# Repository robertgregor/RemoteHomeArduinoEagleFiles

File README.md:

RemoteHomeArduinoEagleFiles
===========================

Remote Home Eagle files for the boards

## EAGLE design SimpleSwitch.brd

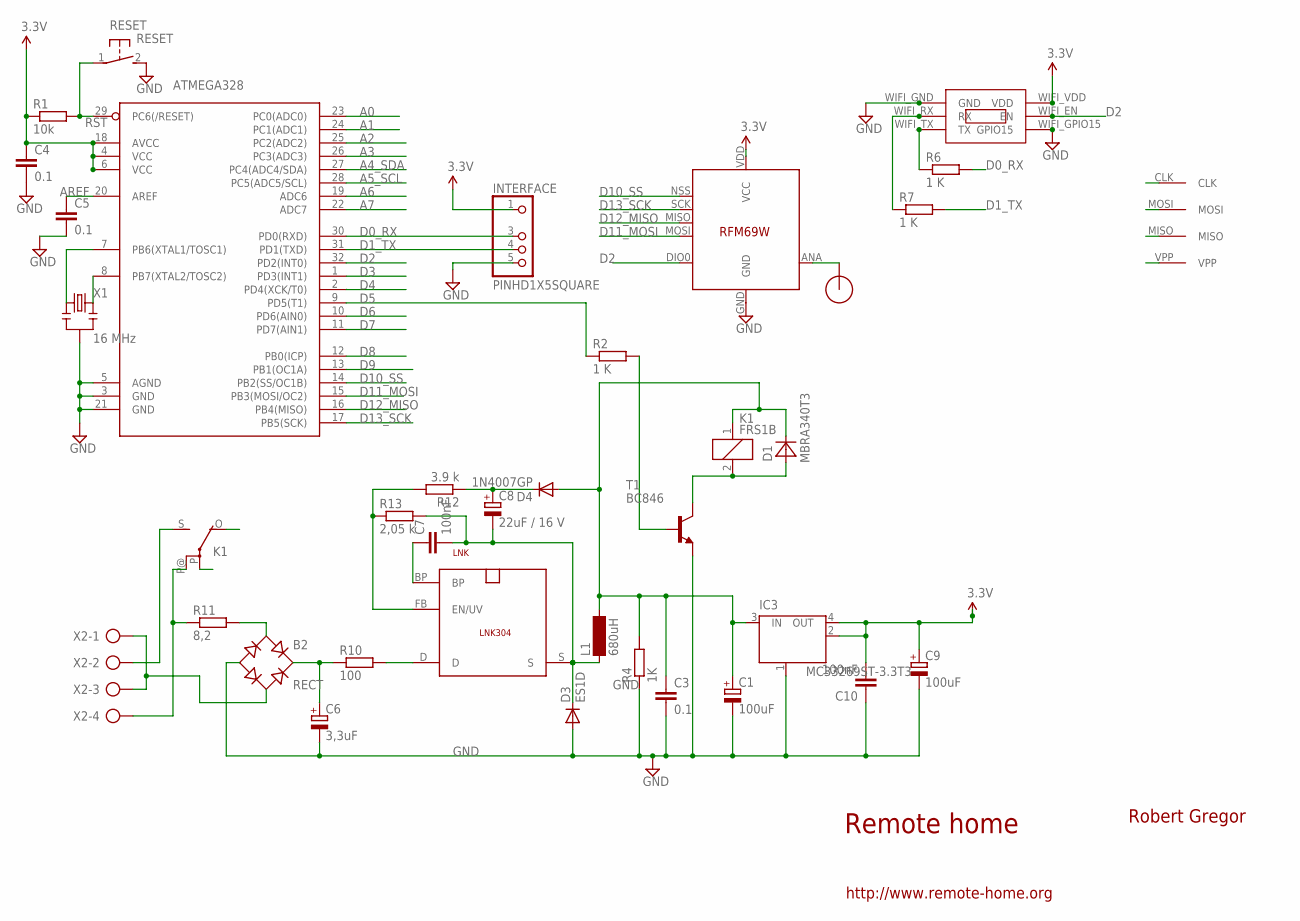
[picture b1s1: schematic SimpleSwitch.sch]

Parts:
ATMEGA328: ATMega-328; TQFP32-08
B2: RECT; TO-269AA
C1, C9: 100uF; SMC_B
C3, C4, C5: 0.1; C2012
C6: 3,3uF; E5-10,5
C7, C10: 100nF; C2012
C8: 22uF / 16 V; SMC_C
D1: MBRA340T3; SMA
D3: ES1D; DO214AC
D4: 1N4007GP; DO214AA
IC3: MC33269ST-3.3T3; SOT223
INTERFACE: PINHD1X5SQUARE; PINHD1X05-SQUARE
K1: FRS1B
L1: 680uH; BS11
LNK: LNK304; SO-8C
R1: 10k; R2012
R2, R6, R7: 1 K; M2012
R4: 1K; M2012
R10: 100; R2512W
R11: 8,2; 0411/12
R12: 3.9 k; M2012
R13: 2,05 k; M2012
RESET: RESET; DTSM-3
RFM69: RFM69W
T1: BC846; SOT23
U$1: RFM12B_ANTENNA; RFM12B-ANTENNA
U$2: AVRHEADERDIP; AVRHEADER
U$5: ESP03
X1: 16 MHz; RESONATOR-SMD
X2: AK500/4

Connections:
5V: C1.+, C3.1, D1.C, D4.A, IC3.3 (IN), K1.1, L1.2, R4.2
A0: ATMEGA328.23 (PC0(ADC0))
A1: ATMEGA328.24 (PC1(ADC1))
A2: ATMEGA328.25 (PC2(ADC2))
A3: ATMEGA328.26 (PC3(ADC3))
A4_SDA: ATMEGA328.27 (PC4(ADC4/SDA))
A5_SCL: ATMEGA328.28 (PC5(ADC5/SCL))
A6: ATMEGA328.19 (ADC6)
A7: ATMEGA328.22 (ADC7)
AREF: ATMEGA328.20 (AREF), C5.1
D0_RX: ATMEGA328.30 (PD0(RXD)), INTERFACE.3, R6.2
D1_TX: ATMEGA328.31 (PD1(TXD)), INTERFACE.4, R7.2
D2: ATMEGA328.32 (PD2(INT0)), RFM69.DIO0, U$5.WIFI_EN (EN)
D3: ATMEGA328.1 (PD3(INT1))
D4: ATMEGA328.2 (PD4(XCK/T0))
D5: ATMEGA328.9 (PD5(T1)), R2.1
D6: ATMEGA328.10 (PD6(AIN0))
D7: ATMEGA328.11 (PD7(AIN1))
D8: ATMEGA328.12 (PB0(ICP))
D9: ATMEGA328.13 (PB1(OC1A))
D10_SS: ATMEGA328.14 (PB2(SS/OC1B)), RFM69.NSS (SEL)
D11_MOSI: ATMEGA328.15 (PB3(MOSI/OC2)), RFM69.MOSI, U$2.MOSI
D12_MISO: ATMEGA328.16 (PB4(MISO)), RFM69.MISO, U$2.MISO
D13_SCK: ATMEGA328.17 (PB5(SCK)), RFM69.SCK, U$2.CLK
FB: LNK.FB (EN/UV), R12.2, R13.1
GND: ATMEGA328.3 (GND), ATMEGA328.5 (AGND), ATMEGA328.21 (GND), B2.-, C1.-, C3.2, C4.2, C5.2, C6.-, C9.-, C10.1, D3.A, IC3.1 (GND/ADJ), INTERFACE.5, R4.1, RESET.2, RFM69.GND, T1.2 (E), U$5.WIFI_GND (GND), U$5.WIFI_GPIO15 (GPIO15), X1.2
unnamed: ATMEGA328.7 (PB6(XTAL1/TOSC1)), X1.1
unnamed: R2.2, T1.1 (B)
unnamed: RFM69.ANA (ANT), U$1.P$1
unnamed: D1.A, K1.2, T1.3 (C)
unnamed: K1.S, X2.2
unnamed: K1.P@, R11.1, X2.4
unnamed: B2.AC2, X2.1, X2.3
unnamed: R6.1, U$5.WIFI_TX (TX)
unnamed: R7.1, U$5.WIFI_RX (RX)
unnamed: LNK.D, R10.2
unnamed: B2.+, C6.+, R10.1
unnamed: B2.AC1, R11.2
unnamed: C7.1, LNK.BP
unnamed: C8.+, D4.C, R12.1
unnamed: ATMEGA328.8 (PB7(XTAL2/TOSC2)), X1.3
RST: ATMEGA328.29 (PC6(/RESET)), R1.2, RESET.1, U$2.VPP
S: C7.2, C8.-, D3.C, L1.1, LNK.S, R13.2
VCC: ATMEGA328.4 (VCC), ATMEGA328.6 (VCC), ATMEGA328.18 (AVCC), C4.1, C9.+, C10.2, IC3.2 (OUT), IC3.4 (OUT), INTERFACE.1, R1.1, RFM69.VDD (VCC), U$5.WIFI_VDD (VDD)

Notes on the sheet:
Remote home
Robert Gregor
http://www.remote-home.org

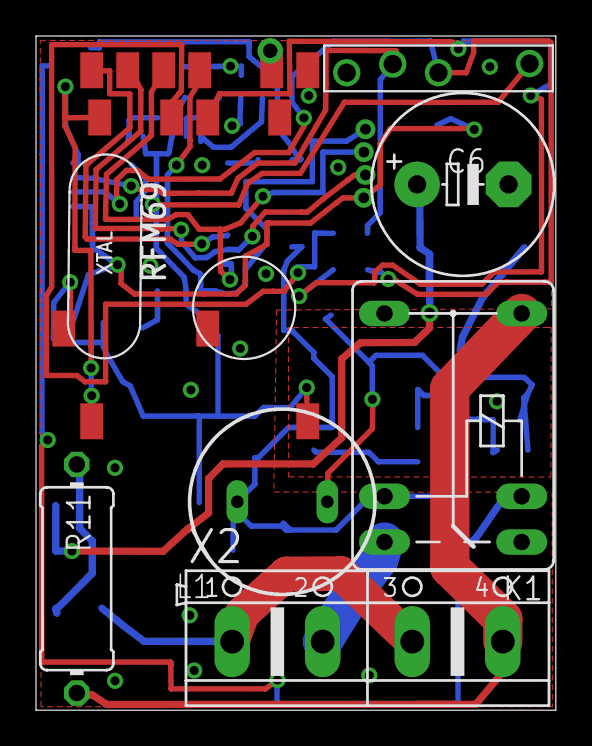
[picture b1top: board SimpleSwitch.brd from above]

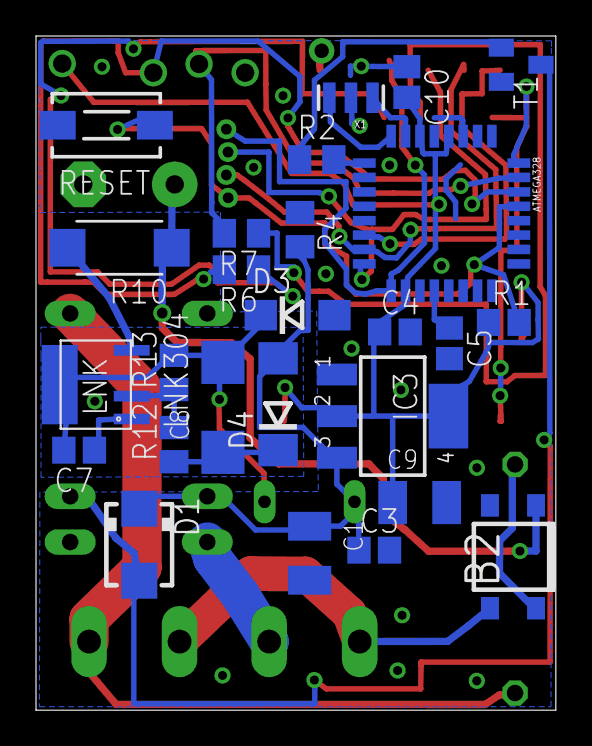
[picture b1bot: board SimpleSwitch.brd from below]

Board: 2 copper layers, 28.9 x 37.5 mm, 36 parts (26 on the bottom side), 30 nets.

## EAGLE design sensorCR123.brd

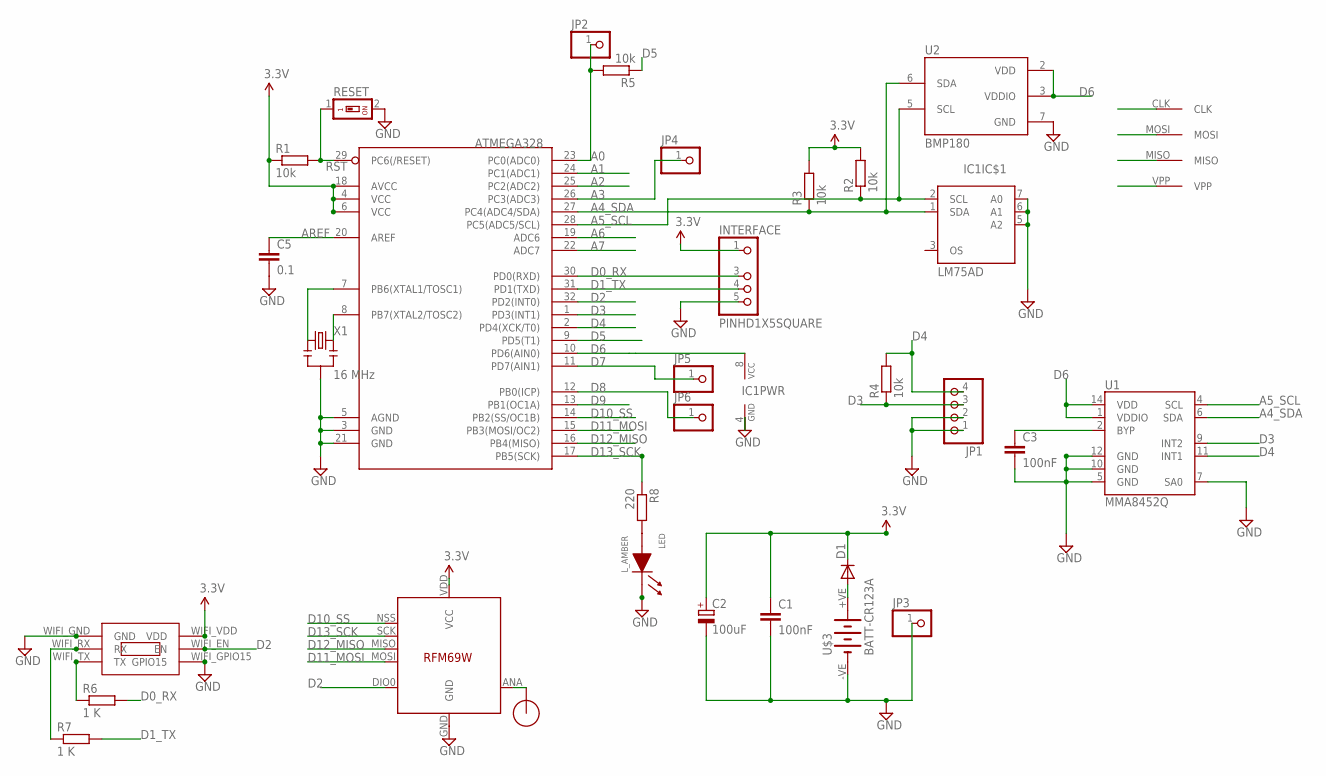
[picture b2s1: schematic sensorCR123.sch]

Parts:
ATMEGA328: ATMega-328; TQFP32-08
C1, C3: 100nF; C2012
C2: 100uF; SMC_B
C5: 0.1; C2012
D1: DIODE-DO214BA; DO214BA
IC1: LM75AD; SO08
INTERFACE: PINHD1X5SQUARE; PINHD1X05-SQUARE
JP1: PINHD-1X04_2.54-S; 1X04-S
JP2, JP3, JP4, JP5, JP6: PINHD-1X01_2.54; 1X01
LED: L_AMBER; LED0805
R1, R2, R3, R4, R5: 10k; R2012
R6, R7: 1 K; M2012
R8: 220; M2012
RESET: SWS001; SMS-001
U1: MMA8452Q; QFN-16_0.5MM
U2: BMP180
U$1: RFM12B_ANTENNA; RFM12B-ANTENNA
U$2: AVRHEADERDIP; AVRHEADER
U$3: BATT-CR123A; KEYSTONE-2/3A
U$4: RFM69W
U$5: ESP03
X1: 16 MHz; RESONATOR-SMD

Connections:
A0: ATMEGA328.23 (PC0(ADC0)), JP2.1, R5.2
A1: ATMEGA328.24 (PC1(ADC1))
A2: ATMEGA328.25 (PC2(ADC2))
A3: ATMEGA328.26 (PC3(ADC3)), JP4.1
A4_SDA: ATMEGA328.27 (PC4(ADC4/SDA)), IC1.1 (SDA), R3.1, U1.6 (SDA), U2.6 (SDA)
A5_SCL: ATMEGA328.28 (PC5(ADC5/SCL)), IC1.2 (SCL), R2.1, U1.4 (SCL), U2.5 (SCL)
A6: ATMEGA328.19 (ADC6)
A7: ATMEGA328.22 (ADC7)
AREF: ATMEGA328.20 (AREF), C5.1
D0_RX: ATMEGA328.30 (PD0(RXD)), INTERFACE.3, R6.2
D1_TX: ATMEGA328.31 (PD1(TXD)), INTERFACE.4, R7.2
D2: ATMEGA328.32 (PD2(INT0)), U$4.DIO0, U$5.WIFI_EN (EN)
D3: ATMEGA328.1 (PD3(INT1)), JP1.3, R4.1, U1.9 (INT2)
D4: ATMEGA328.2 (PD4(XCK/T0)), JP1.4, R4.2, U1.11 (INT1)
D5: ATMEGA328.9 (PD5(T1)), R5.1
D6: ATMEGA328.10 (PD6(AIN0)), IC1.8 (VCC), U1.1 (VDDIO), U1.14 (VDD), U2.2 (VDD), U2.3 (VDDIO)
D7: ATMEGA328.11 (PD7(AIN1)), JP5.1
D8: ATMEGA328.12 (PB0(ICP)), JP6.1
D9: ATMEGA328.13 (PB1(OC1A))
D10_SS: ATMEGA328.14 (PB2(SS/OC1B)), U$4.NSS (SEL)
D11_MOSI: ATMEGA328.15 (PB3(MOSI/OC2)), U$2.MOSI, U$4.MOSI
D12_MISO: ATMEGA328.16 (PB4(MISO)), U$2.MISO, U$4.MISO
D13_SCK: ATMEGA328.17 (PB5(SCK)), R8.1, U$2.CLK, U$4.SCK
GND: ATMEGA328.3 (GND), ATMEGA328.5 (AGND), ATMEGA328.21 (GND), C1.2, C2.-, C3.2, C5.2, IC1.4 (GND), IC1.5 (A2), IC1.6 (A1), IC1.7 (A0), INTERFACE.5, JP1.1, JP1.2, JP3.1, LED.1 (CA), RESET.2, U1.5 (GND), U1.7 (SA0), U1.10 (GND), U1.12 (GND), U2.7 (GND), U$3.-VE (-), U$4.GND, U$5.WIFI_GND (GND), U$5.WIFI_GPIO15 (GPIO15), X1.2
unnamed: ATMEGA328.7 (PB6(XTAL1/TOSC1)), X1.1
unnamed: C3.1, U1.2 (BYP)
unnamed: U$1.P$1, U$4.ANA (ANT)
unnamed: LED.2 (AN), R8.2
unnamed: D1.A, U$3.+VE (+)
unnamed: R6.1, U$5.WIFI_TX (TX)
unnamed: R7.1, U$5.WIFI_RX (RX)
unnamed: ATMEGA328.8 (PB7(XTAL2/TOSC2)), X1.3
RST: ATMEGA328.29 (PC6(/RESET)), R1.2, RESET.1, U$2.VPP
VCC: ATMEGA328.4 (VCC), ATMEGA328.6 (VCC), ATMEGA328.18 (AVCC), C1.1, C2.+, D1.C, INTERFACE.1, R1.1, R2.2, R3.2, U$4.VDD (VCC), U$5.WIFI_VDD (VDD)

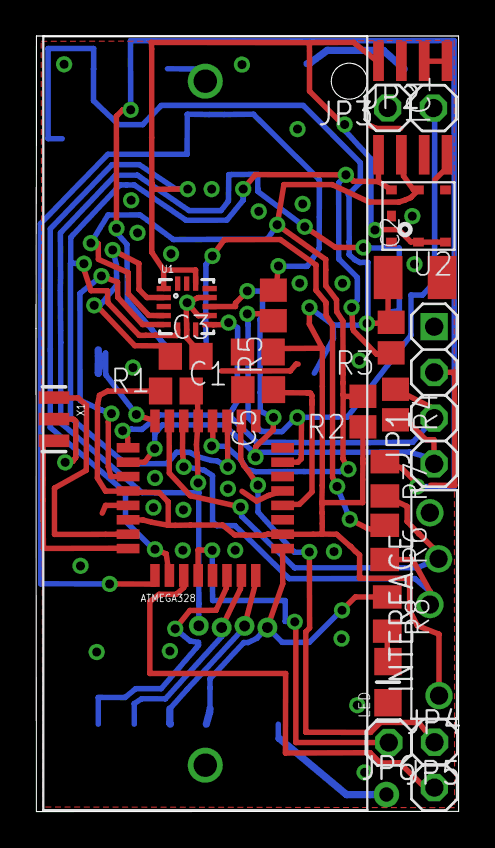
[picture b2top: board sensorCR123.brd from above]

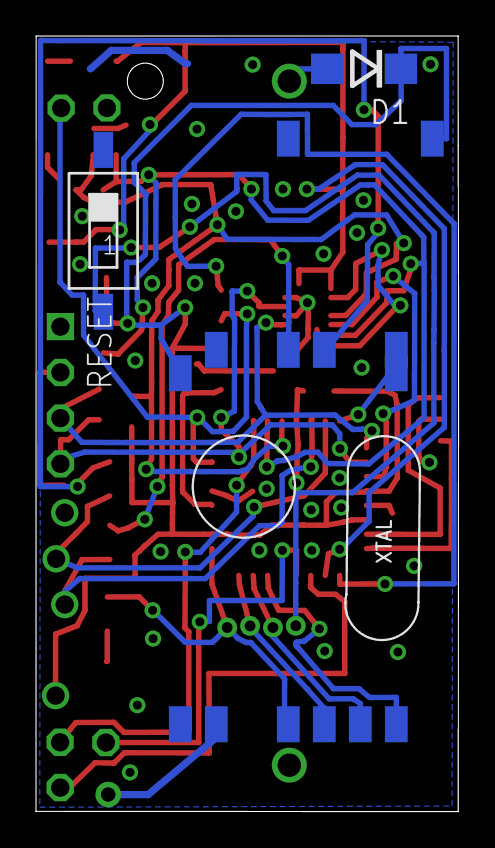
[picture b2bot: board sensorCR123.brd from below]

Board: 2 copper layers, 23.5 x 43.1 mm, 32 parts (4 on the bottom side), 29 nets.

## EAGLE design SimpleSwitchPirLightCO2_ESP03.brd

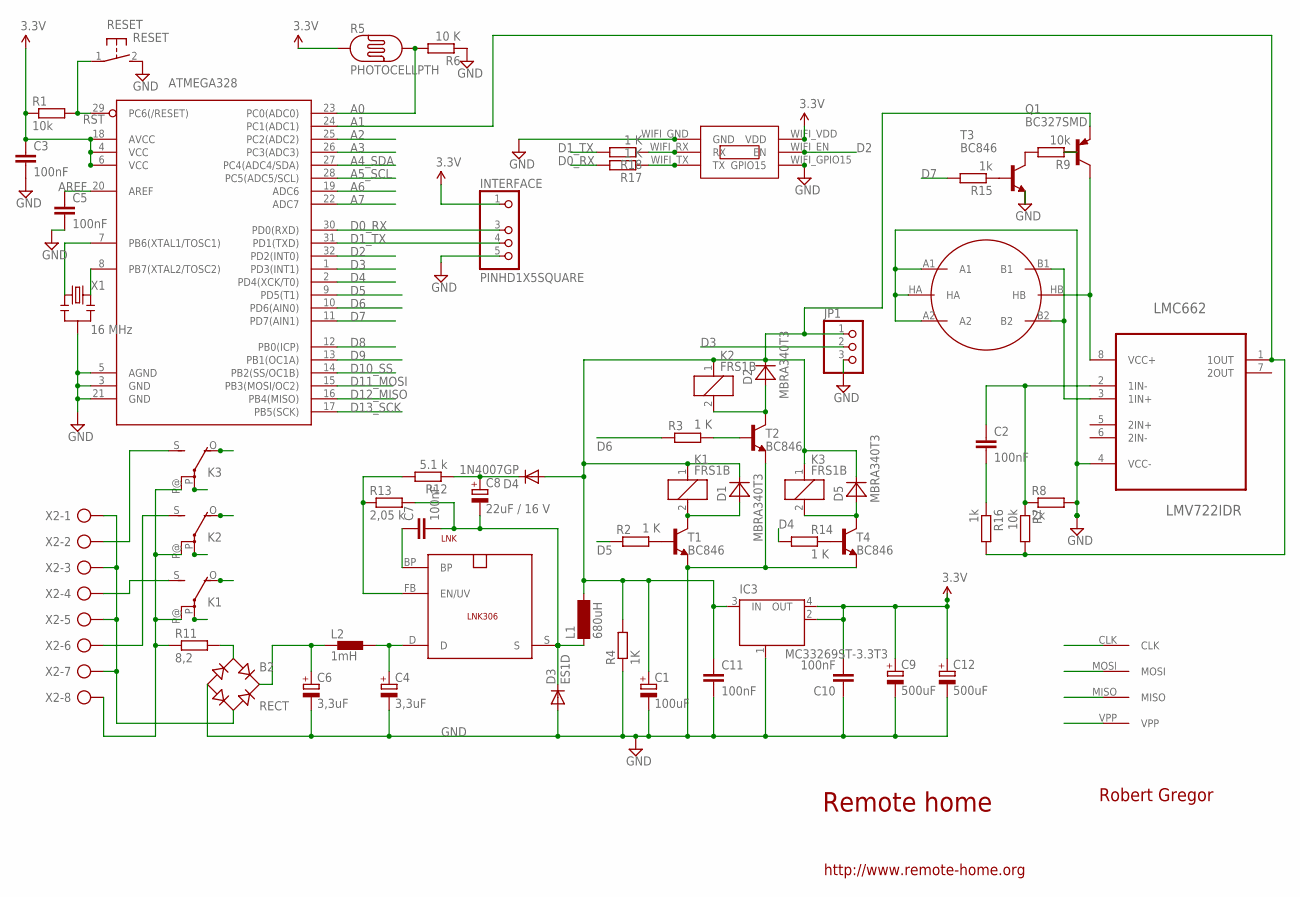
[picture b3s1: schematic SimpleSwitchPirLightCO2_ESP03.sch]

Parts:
ATMEGA328: ATMega-328; TQFP32-08
B2: RECT; TO-269AA
C1: 100uF; SMC_B
C2, C3, C5, C7, C10, C11: 100nF; C2012
C4, C6: 3,3uF; E5-10,5
C8: 22uF / 16 V; SMC_C
C9, C12: 500uF; SMC_D
D1, D2, D5: MBRA340T3; SMA
D3: ES1D; DO214AC
D4: 1N4007GP; DO214AA
IC3: MC33269ST-3.3T3; SOT223
INTERFACE: PINHD1X5SQUARE; PINHD1X05-SQUARE
JP1: PINHD-1X03_2.54-S; 1X03-S
K1, K2, K3: FRS1B
L1: 680uH; BS11
L2: 1mH; BL02RN1
LMC662: LMV722IDR; SOIC127P600X175-8N
LNK: LNK306; SO-8C
Q1: BC327SMD; SOT23-BEC
R1, R7, R9: 10k; R2012
R2, R3, R14, R17, R18: 1 K; M2012
R4: 1K; M2012
R5: PHOTOCELLPTH; PHOTOCELL
R6: 10 K; M2012
R8: 2k; R2012
R11: 8,2; 0411/12
R12: 5.1 k; M2012
R13: 2,05 k; M2012
R15, R16: 1k; R2012
RESET: RESET; DTSM-3
T1, T2, T3, T4: BC846; SOT23
U$2: AVRHEADERDIP; AVRHEADER
U$4: METHANE_SENSOR; MQ-3
U$5: ESP03
X1: 16 MHz; RESONATOR-SMD
X2: AK500/8

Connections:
6V: C1.+, C11.1, D1.C, D2.C, D4.A, D5.C, IC3.3 (IN), JP1.1, K1.1, K2.1, K3.1, L1.2, Q1.E, R4.2
A0: ATMEGA328.23 (PC0(ADC0)), R5.2, R6.2
A1: ATMEGA328.24 (PC1(ADC1)), LMC662.1 (1OUT), R7.2, R16.2
A2: ATMEGA328.25 (PC2(ADC2))
A3: ATMEGA328.26 (PC3(ADC3))
A4_SDA: ATMEGA328.27 (PC4(ADC4/SDA))
A5_SCL: ATMEGA328.28 (PC5(ADC5/SCL))
A6: ATMEGA328.19 (ADC6)
A7: ATMEGA328.22 (ADC7)
AREF: ATMEGA328.20 (AREF), C5.1
D0_RX: ATMEGA328.30 (PD0(RXD)), INTERFACE.3, R17.2
D1_TX: ATMEGA328.31 (PD1(TXD)), INTERFACE.4, R18.2
D2: ATMEGA328.32 (PD2(INT0)), U$5.WIFI_EN (EN)
D3: ATMEGA328.1 (PD3(INT1)), JP1.2
D4: ATMEGA328.2 (PD4(XCK/T0)), R14.1
D5: ATMEGA328.9 (PD5(T1)), R2.1
D6: ATMEGA328.10 (PD6(AIN0)), R3.1
D7: ATMEGA328.11 (PD7(AIN1)), R15.2
D8: ATMEGA328.12 (PB0(ICP))
D9: ATMEGA328.13 (PB1(OC1A))
D10_SS: ATMEGA328.14 (PB2(SS/OC1B))
D11_MOSI: ATMEGA328.15 (PB3(MOSI/OC2)), U$2.MOSI
D12_MISO: ATMEGA328.16 (PB4(MISO)), U$2.MISO
D13_SCK: ATMEGA328.17 (PB5(SCK)), U$2.CLK
FB: LNK.FB (EN/UV), R12.2, R13.1
GND: ATMEGA328.3 (GND), ATMEGA328.5 (AGND), ATMEGA328.21 (GND), B2.-, C1.-, C3.2, C4.-, C5.2, C6.-, C9.-, C10.1, C11.2, C12.-, D3.A, IC3.1 (GND/ADJ), INTERFACE.5, JP1.3, LMC662.4 (VCC-), R4.1, R6.1, R8.2, RESET.2, T1.2 (E), T2.2 (E), T3.2 (E), T4.2 (E), U$4.A1, U$4.A2, U$4.HA, U$5.WIFI_GND (GND), U$5.WIFI_GPIO15 (GPIO15), X1.2
unnamed: ATMEGA328.7 (PB6(XTAL1/TOSC1)), X1.1
unnamed: R2.2, T1.1 (B)
unnamed: LMC662.3 (1IN+), U$4.B1, U$4.B2
unnamed: D1.A, K1.2, T1.3 (C)
unnamed: K3.S, X2.2
unnamed: K2.S, X2.6
unnamed: K1.P@, K2.P@, K3.P@, R11.1, X2.8
unnamed: B2.AC2, X2.1, X2.3, X2.5, X2.7
unnamed: D5.A, K3.2, T4.3 (C)
unnamed: D2.A, K2.2, T2.3 (C)
unnamed: R3.2, T2.1 (B)
unnamed: C4.+, L2.2, LNK.D
unnamed: B2.+, C6.+, L2.1
unnamed: B2.AC1, R11.2
unnamed: K1.S, X2.4
unnamed: C2.1, LMC662.2 (1IN-), R7.1, R8.1
unnamed: C7.1, LNK.BP
unnamed: LMC662.8 (VCC+), Q1.C, U$4.HB
unnamed: C8.+, D4.C, R12.1
unnamed: ATMEGA328.8 (PB7(XTAL2/TOSC2)), X1.3
unnamed: R15.1, T3.1 (B)
unnamed: R9.2, T3.3 (C)
unnamed: Q1.B, R9.1
unnamed: C2.2, R16.1
unnamed: R14.2, T4.1 (B)
unnamed: R17.1, U$5.WIFI_TX (TX)
unnamed: R18.1, U$5.WIFI_RX (RX)
RST: ATMEGA328.29 (PC6(/RESET)), R1.2, RESET.1, U$2.VPP
S: C7.2, C8.-, D3.C, L1.1, LNK.S, R13.2
VCC: ATMEGA328.4 (VCC), ATMEGA328.6 (VCC), ATMEGA328.18 (AVCC), C3.1, C9.+, C10.2, C12.+, IC3.2 (OUT), IC3.4 (OUT), INTERFACE.1, R1.1, R5.1, U$5.WIFI_VDD (VDD)

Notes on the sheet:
Remote home
Robert Gregor
http://www.remote-home.org

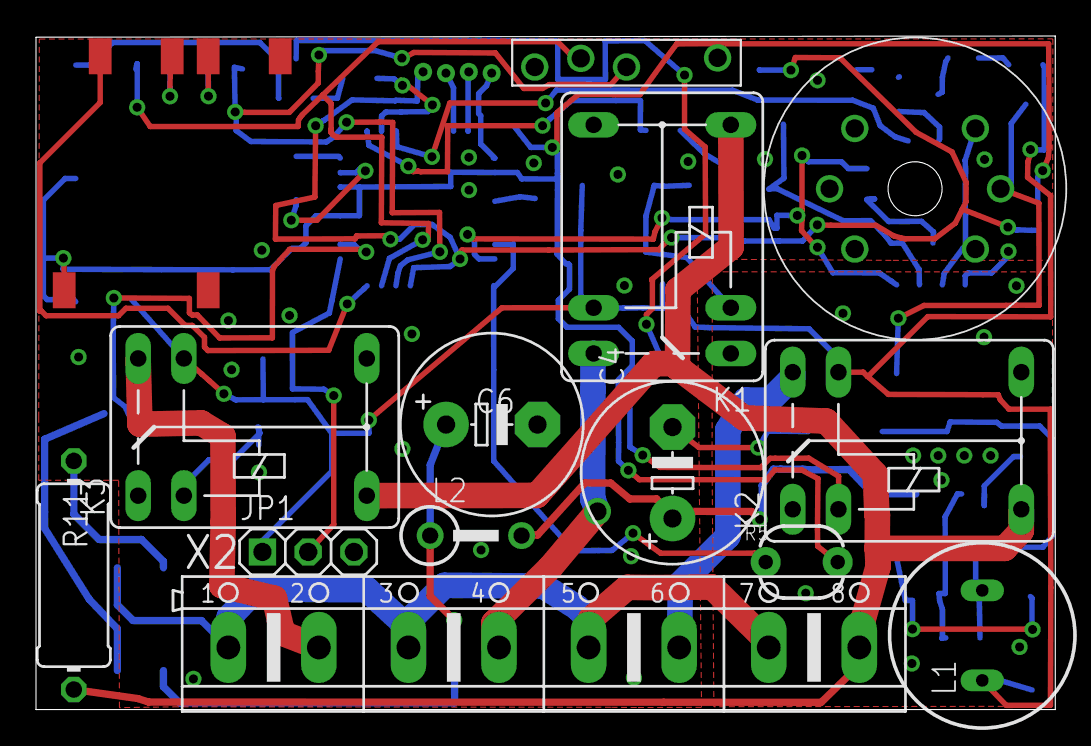
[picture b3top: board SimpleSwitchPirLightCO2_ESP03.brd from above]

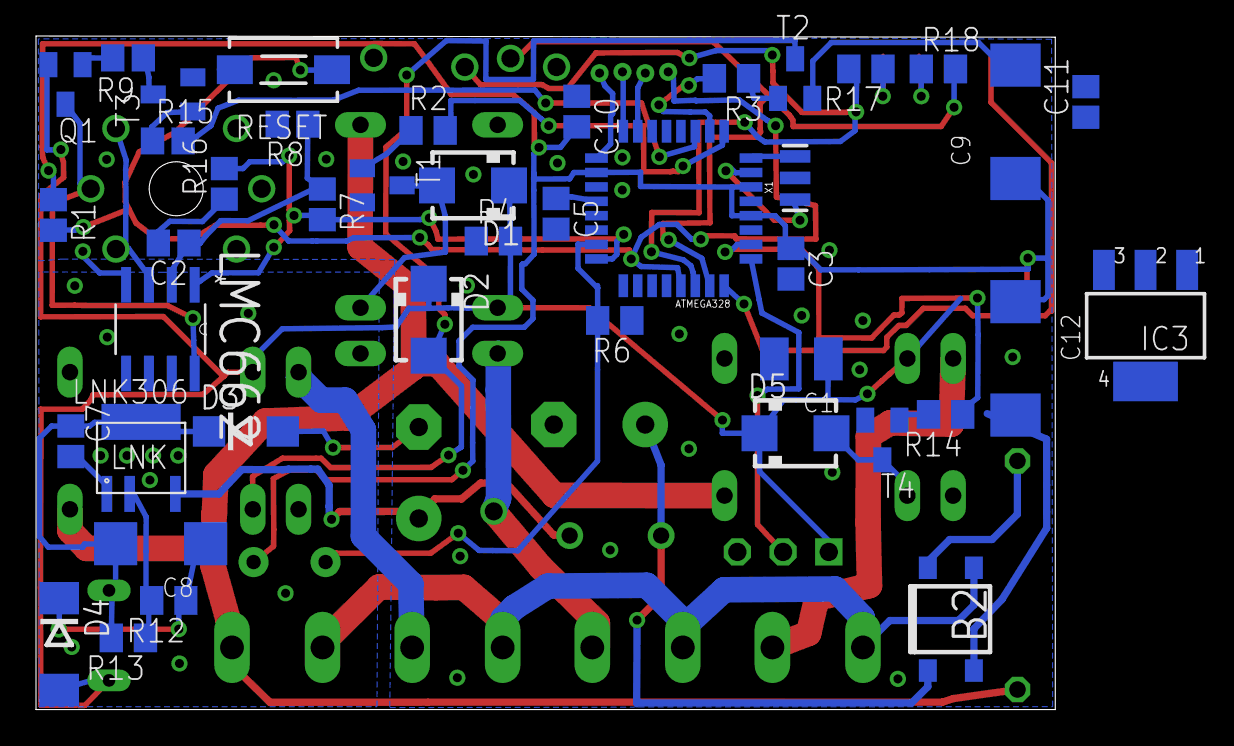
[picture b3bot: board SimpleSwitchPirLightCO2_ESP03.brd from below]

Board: 2 copper layers, 56.6 x 37.4 mm, 57 parts (42 on the bottom side), 47 nets.

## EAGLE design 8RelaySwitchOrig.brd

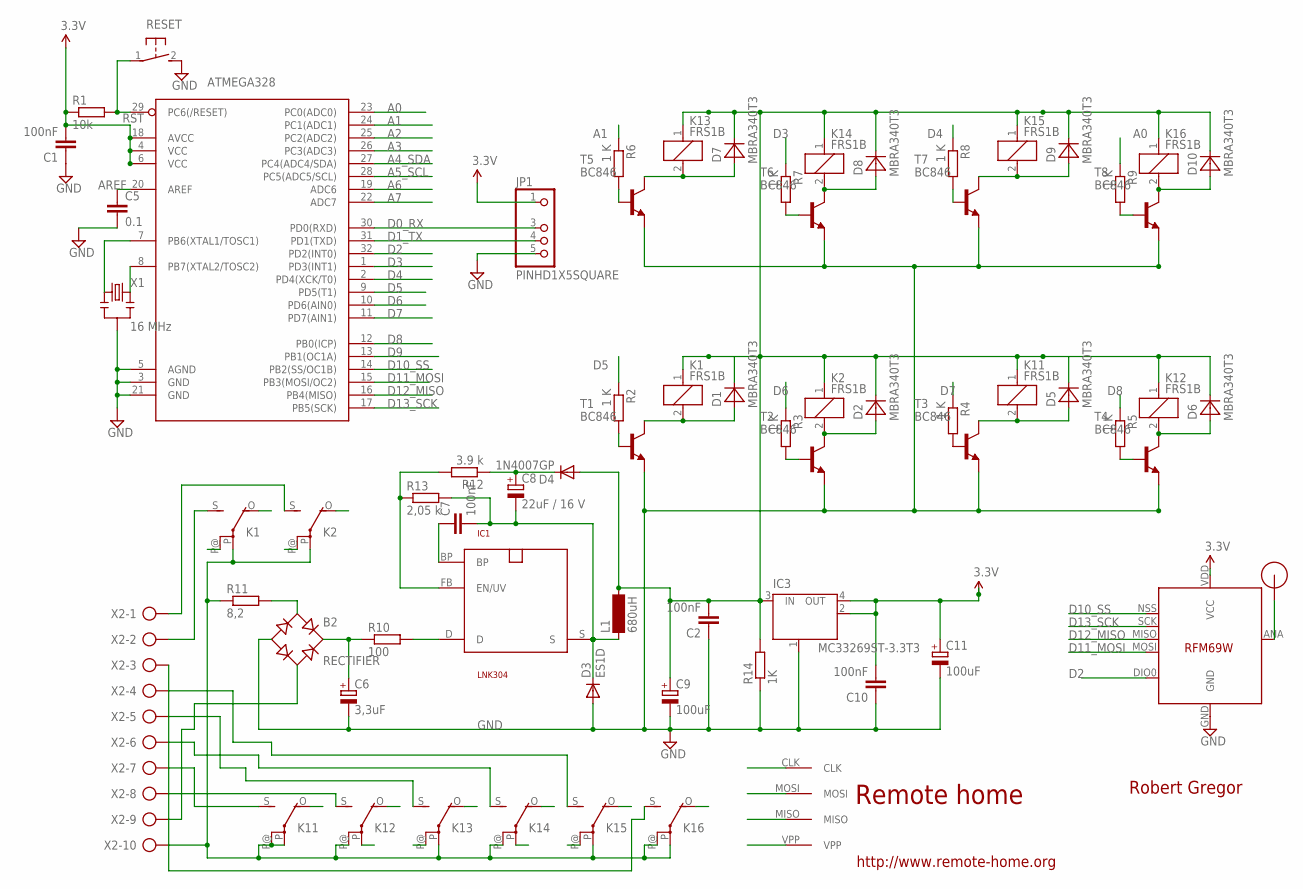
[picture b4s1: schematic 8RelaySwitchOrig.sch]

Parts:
ATMEGA328: ATMega-328; TQFP32-08
B2: RECTIFIER; TO-269AA
C1, C2, C7, C10: 100nF; C2012
C5: 0.1; C2012
C6: 3,3uF; E5-10,5
C8: 22uF / 16 V; SMC_C
C9, C11: 100uF; SMC_B
D1, D2, D5, D6, D7, D8, D9, D10: MBRA340T3; SMA
D3: ES1D; DO214AC
D4: 1N4007GP; DO214AA
IC1: LNK304; SO-8C
IC3: MC33269ST-3.3T3; SOT223
JP1: PINHD1X5SQUARE; PINHD1X05-SQUARE
K1, K2, K11, K12, K13, K14, K15, K16: FRS1B
L1: 680uH; SD8
R1: 10k; R2012
R2, R3, R4, R5, R6, R7, R8, R9: 1 K; M2012
R10: 100; R2512W
R11: 8,2; 0411/12
R12: 3.9 k; M2012
R13: 2,05 k; M2012
R14: 1K; M2012
RESET: DTSM-3
T1, T2, T3, T4, T5, T6, T7, T8: BC846; SOT23
U$1: RFM12B_ANTENNA; RFM12B-ANTENNA
U$2: AVRHEADERDIP; AVRHEADER
U$5: RFM69; RFM69W-MINPADS
X1: 16 MHz; RESONATOR-SMD
X2: AK500/10

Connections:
5V1: C2.2, C9.+, D1.C, D2.C, D4.A, D5.C, D6.C, D7.C, D8.C, D9.C, D10.C, IC3.3 (IN), K1.1, K2.1, K11.1, K12.1, K13.1, K14.1, K15.1, K16.1, L1.2, R14.2
A0: ATMEGA328.23 (PC0(ADC0)), R9.1
A1: ATMEGA328.24 (PC1(ADC1)), R6.1
A2: ATMEGA328.25 (PC2(ADC2))
A3: ATMEGA328.26 (PC3(ADC3))
A4_SDA: ATMEGA328.27 (PC4(ADC4/SDA))
A5_SCL: ATMEGA328.28 (PC5(ADC5/SCL))
A6: ATMEGA328.19 (ADC6)
A7: ATMEGA328.22 (ADC7)
AREF: ATMEGA328.20 (AREF), C5.1
D0_RX: ATMEGA328.30 (PD0(RXD)), JP1.3
D1_TX: ATMEGA328.31 (PD1(TXD)), JP1.4
D2: ATMEGA328.32 (PD2(INT0)), U$5.DIO0
D3: ATMEGA328.1 (PD3(INT1)), R7.1
D4: ATMEGA328.2 (PD4(XCK/T0)), R8.1
D5: ATMEGA328.9 (PD5(T1)), R2.1
D6: ATMEGA328.10 (PD6(AIN0)), R3.1
D7: ATMEGA328.11 (PD7(AIN1)), R4.1
D8: ATMEGA328.12 (PB0(ICP)), R5.1
D9: ATMEGA328.13 (PB1(OC1A))
D10_SS: ATMEGA328.14 (PB2(SS/OC1B)), U$5.NSS (SEL)
D11_MOSI: ATMEGA328.15 (PB3(MOSI/OC2)), U$2.MOSI, U$5.MOSI
D12_MISO: ATMEGA328.16 (PB4(MISO)), U$2.MISO, U$5.MISO
D13_SCK: ATMEGA328.17 (PB5(SCK)), U$2.CLK, U$5.SCK
GND: ATMEGA328.3 (GND), ATMEGA328.5 (AGND), ATMEGA328.21 (GND), B2.-, C1.1, C2.1, C5.2, C6.-, C9.-, C10.1, C11.-, D3.A, IC3.1 (GND/ADJ), JP1.5, R14.1, RESET.2, T1.2 (E), T2.2 (E), T3.2 (E), T4.2 (E), T5.2 (E), T6.2 (E), T7.2 (E), T8.2 (E), U$5.GND, X1.2
unnamed: ATMEGA328.7 (PB6(XTAL1/TOSC1)), X1.1
unnamed: R2.2, T1.1 (B)
unnamed: U$1.P$1, U$5.ANA (ANT)
unnamed: D2.A, K2.2, T2.3 (C)
unnamed: D1.A, K1.2, T1.3 (C)
unnamed: R3.2, T2.1 (B)
unnamed: K1.S, X2.2
unnamed: B2.AC2, X2.9
unnamed: IC1.D, R10.2
unnamed: B2.+, C6.+, R10.1
unnamed: B2.AC1, R11.2
unnamed: C7.1, IC1.BP
unnamed: C8.+, D4.C, R12.1
unnamed: ATMEGA328.8 (PB7(XTAL2/TOSC2)), X1.3
unnamed: D5.A, K11.2, T3.3 (C)
unnamed: R4.2, T3.1 (B)
unnamed: D6.A, K12.2, T4.3 (C)
unnamed: R5.2, T4.1 (B)
unnamed: D7.A, K13.2, T5.3 (C)
unnamed: R6.2, T5.1 (B)
unnamed: D8.A, K14.2, T6.3 (C)
unnamed: R7.2, T6.1 (B)
unnamed: D9.A, K15.2, T7.3 (C)
unnamed: R8.2, T7.1 (B)
unnamed: D10.A, K16.2, T8.3 (C)
unnamed: R9.2, T8.1 (B)
unnamed: K12.S, X2.8
unnamed: K11.S, X2.7
unnamed: K1.P, K2.P, K11.P, K11.P@, K12.P@, K13.P, K14.P@, K15.P, K16.P, K16.P@, R11.1, X2.10
unnamed: K16.S, X2.3
unnamed: K2.S, X2.1
unnamed: K13.S, X2.5
unnamed: K14.S, X2.6
unnamed: K15.S, X2.4
RST: ATMEGA328.29 (PC6(/RESET)), R1.2, RESET.1, U$2.VPP
S: C7.2, C8.-, D3.C, IC1.S, L1.1, R13.2
VCC: ATMEGA328.4 (VCC), ATMEGA328.6 (VCC), ATMEGA328.18 (AVCC), C1.2, C10.2, C11.+, IC3.2 (OUT), IC3.4 (OUT), JP1.1, R1.1, U$5.VDD (VCC)
XXX: IC1.FB (EN/UV), R12.2, R13.1

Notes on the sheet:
Remote home
Robert Gregor
http://www.remote-home.org

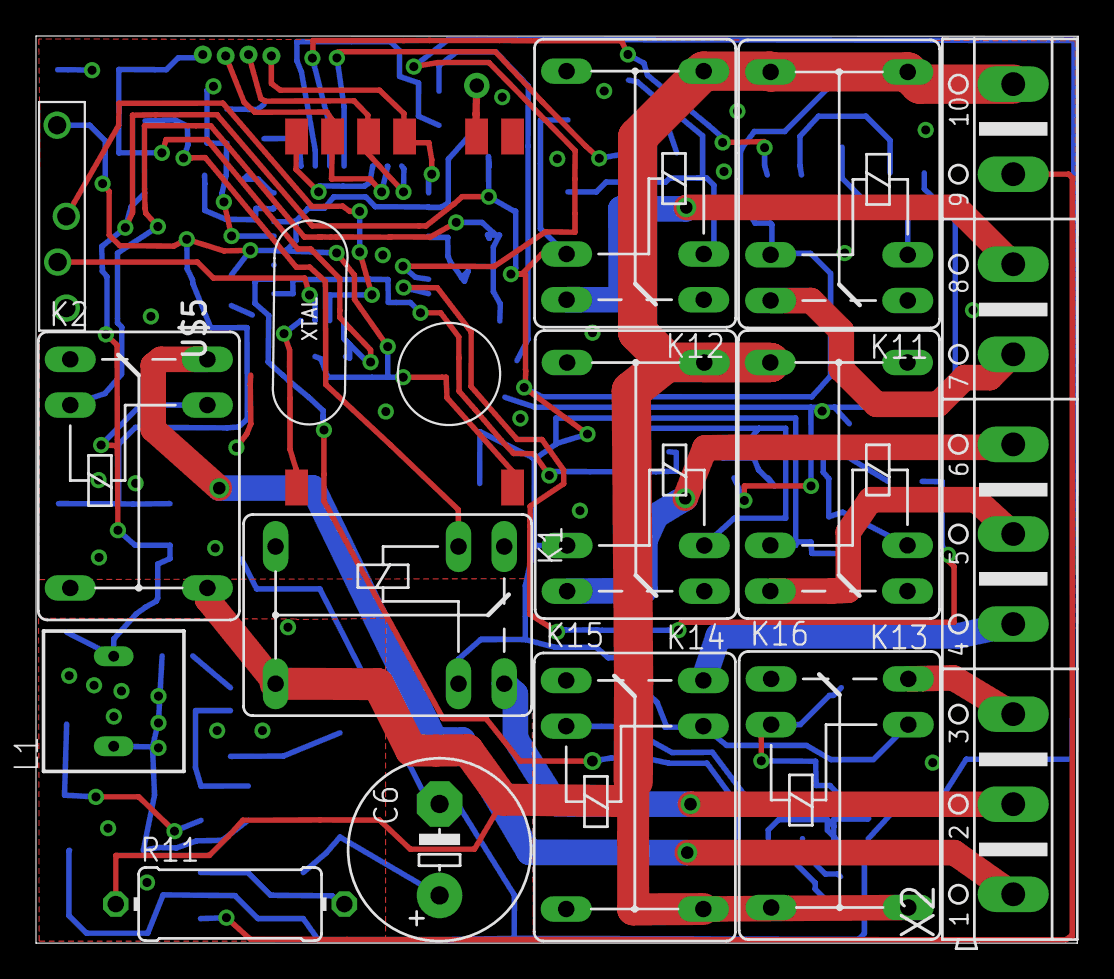
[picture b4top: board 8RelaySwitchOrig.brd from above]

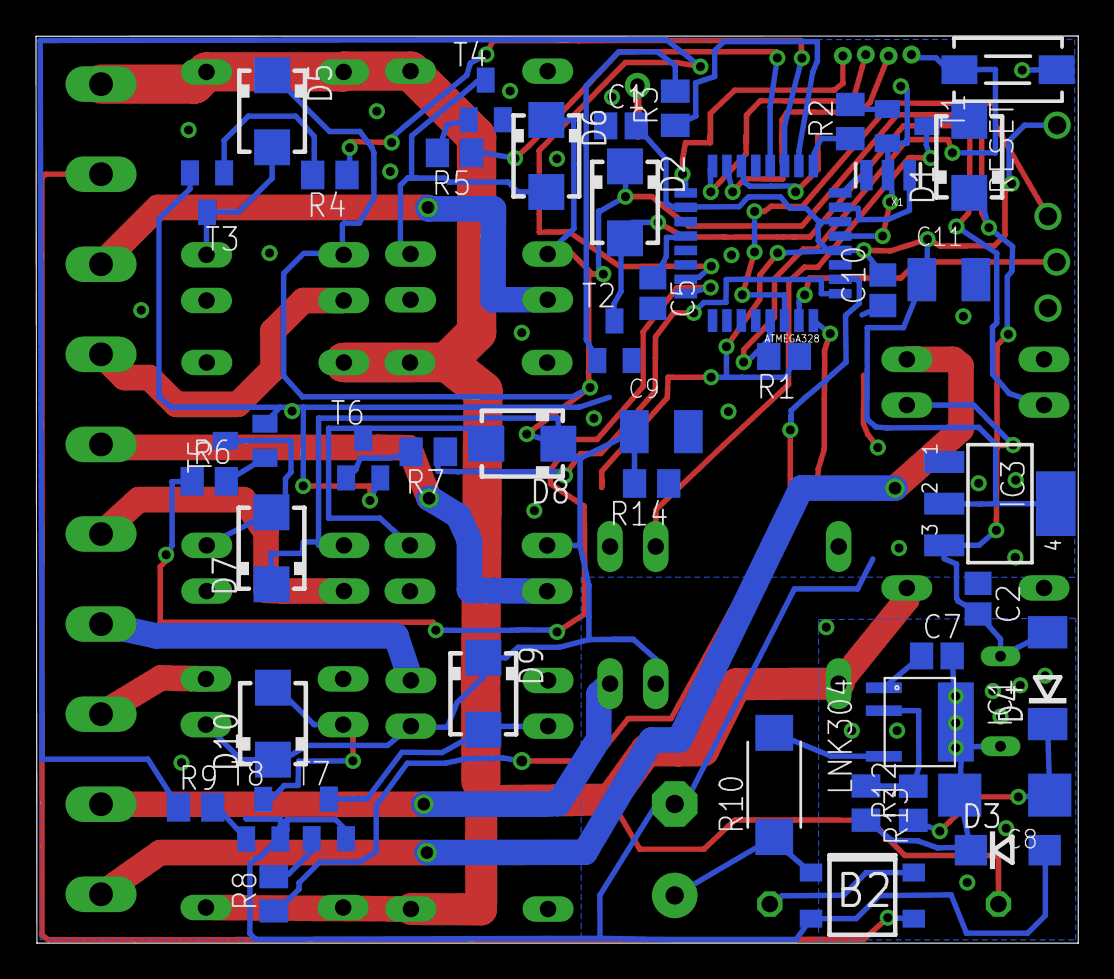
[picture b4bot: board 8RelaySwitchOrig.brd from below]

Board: 2 copper layers, 57.9 x 50.4 mm, 61 parts (45 on the bottom side), 56 nets.

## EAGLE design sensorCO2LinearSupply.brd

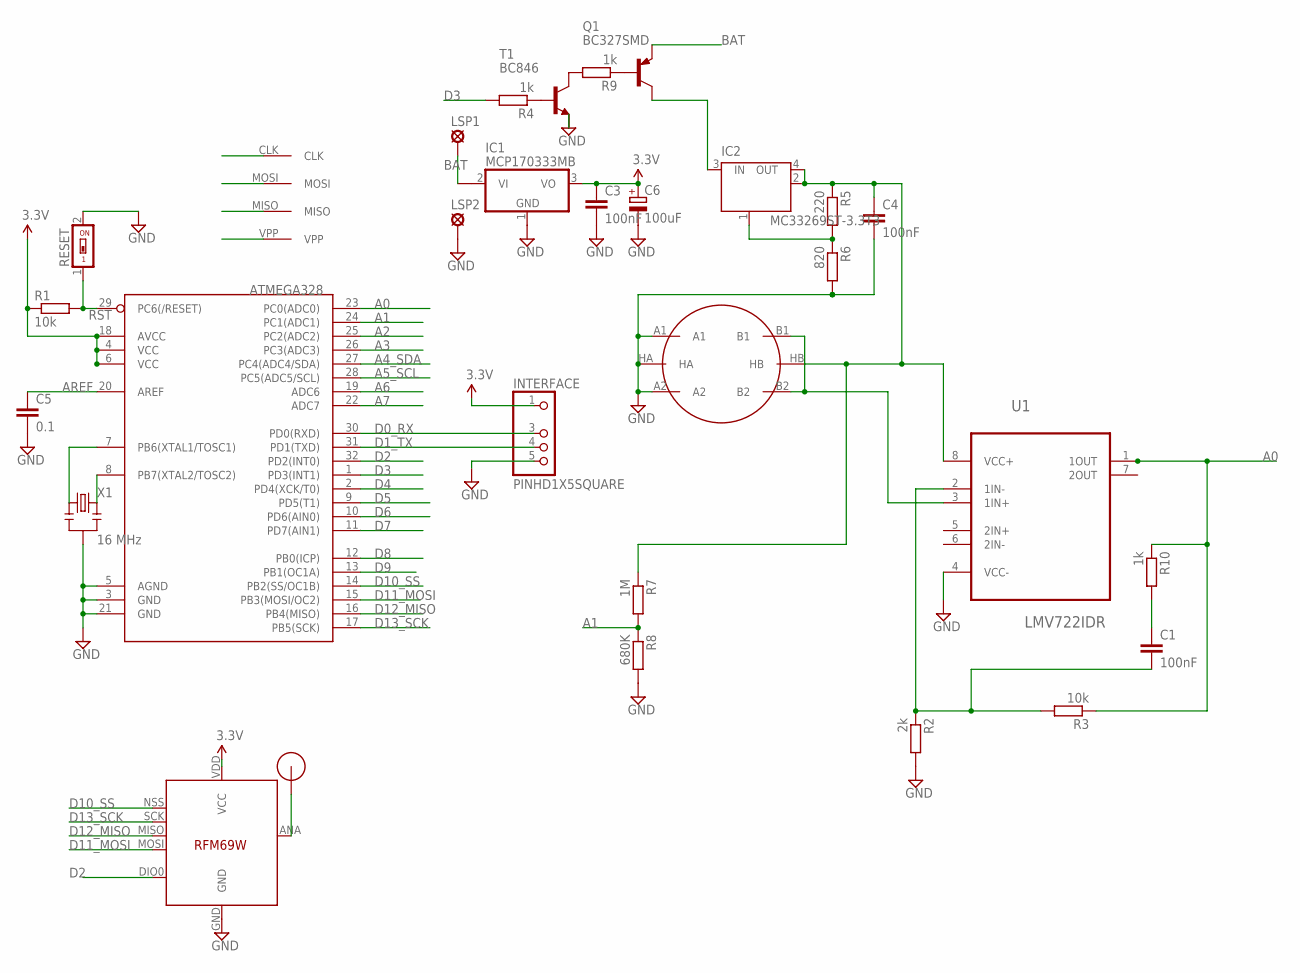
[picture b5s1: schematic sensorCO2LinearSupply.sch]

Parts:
ATMEGA328: ATMega-328; TQFP32-08
C1, C3, C4: 100nF; C2012
C5: 0.1; C2012
C6: 100uF; SMC_B
IC1: MCP170333MB; SOT89
IC2: MC33269ST-3.3T3; SOT223
IC4: RFM69; RFM69W-MINPADS
INTERFACE: PINHD1X5SQUARE; PINHD1X05-SQUARE
LSP1, LSP2: LSP11
Q1: BC327SMD; SOT23-BEC
R1, R3: 10k; R2012
R2: 2k; R2012
R4, R9, R10: 1k; R2012
R5: 220; R2012
R6: 820; R2012
R7: 1M; R2012
R8: 680K; R2012
RESET: SWS001; SMS-001
T1: BC846; SOT23
U1: LMV722IDR; SOIC127P600X175-8N
U$1: RFM12B_ANTENNA; RFM12B-ANTENNA
U$2: AVRHEADERDIP; AVRHEADER
U$4: METHANE_SENSOR; MQ-3
X1: 16 MHz; RESONATOR-SMD

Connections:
6V: C4.1, IC2.2 (OUT), IC2.4 (OUT), R5.1, R7.1, U1.8 (VCC+), U$4.HB
A0: ATMEGA328.23 (PC0(ADC0)), R3.1, R10.1, U1.1 (1OUT)
A1: ATMEGA328.24 (PC1(ADC1)), R7.2, R8.1
A2: ATMEGA328.25 (PC2(ADC2))
A3: ATMEGA328.26 (PC3(ADC3))
A4_SDA: ATMEGA328.27 (PC4(ADC4/SDA))
A5_SCL: ATMEGA328.28 (PC5(ADC5/SCL))
A6: ATMEGA328.19 (ADC6)
A7: ATMEGA328.22 (ADC7)
AREF: ATMEGA328.20 (AREF), C5.1
BAT: IC1.2@1 (VI1), LSP1.MP, Q1.E
D0_RX: ATMEGA328.30 (PD0(RXD)), INTERFACE.3
D1_TX: ATMEGA328.31 (PD1(TXD)), INTERFACE.4
D2: ATMEGA328.32 (PD2(INT0)), IC4.DIO0
D3: ATMEGA328.1 (PD3(INT1)), R4.2
D4: ATMEGA328.2 (PD4(XCK/T0))
D5: ATMEGA328.9 (PD5(T1))
D6: ATMEGA328.10 (PD6(AIN0))
D7: ATMEGA328.11 (PD7(AIN1))
D8: ATMEGA328.12 (PB0(ICP))
D9: ATMEGA328.13 (PB1(OC1A))
D10_SS: ATMEGA328.14 (PB2(SS/OC1B)), IC4.NSS (SEL)
D11_MOSI: ATMEGA328.15 (PB3(MOSI/OC2)), IC4.MOSI, U$2.MOSI
D12_MISO: ATMEGA328.16 (PB4(MISO)), IC4.MISO, U$2.MISO
D13_SCK: ATMEGA328.17 (PB5(SCK)), IC4.SCK, U$2.CLK
GND: ATMEGA328.3 (GND), ATMEGA328.5 (AGND), ATMEGA328.21 (GND), C3.2, C4.2, C5.2, C6.-, IC1.1 (GND), IC4.GND, INTERFACE.5, LSP2.MP, R2.2, R6.2, R8.2, RESET.2, T1.2 (E), U1.4 (VCC-), U$4.A1, U$4.A2, U$4.HA, X1.2
unnamed: ATMEGA328.7 (PB6(XTAL1/TOSC1)), X1.1
unnamed: IC2.1 (GND/ADJ), R5.2, R6.1
unnamed: IC4.ANA (ANT), U$1.P$1
unnamed: IC2.3 (IN), Q1.C
unnamed: C1.1, R10.2
unnamed: U1.3 (1IN+), U$4.B1, U$4.B2
unnamed: R4.1, T1.1 (B)
unnamed: R9.2, T1.3 (C)
unnamed: Q1.B, R9.1
unnamed: C1.2, R2.1, R3.2, U1.2 (1IN-)
unnamed: ATMEGA328.8 (PB7(XTAL2/TOSC2)), X1.3
RST: ATMEGA328.29 (PC6(/RESET)), R1.2, RESET.1, U$2.VPP
VCC: ATMEGA328.4 (VCC), ATMEGA328.6 (VCC), ATMEGA328.18 (AVCC), C3.1, C6.+, IC1.3 (VO), IC4.VDD (VCC), INTERFACE.1, R1.1

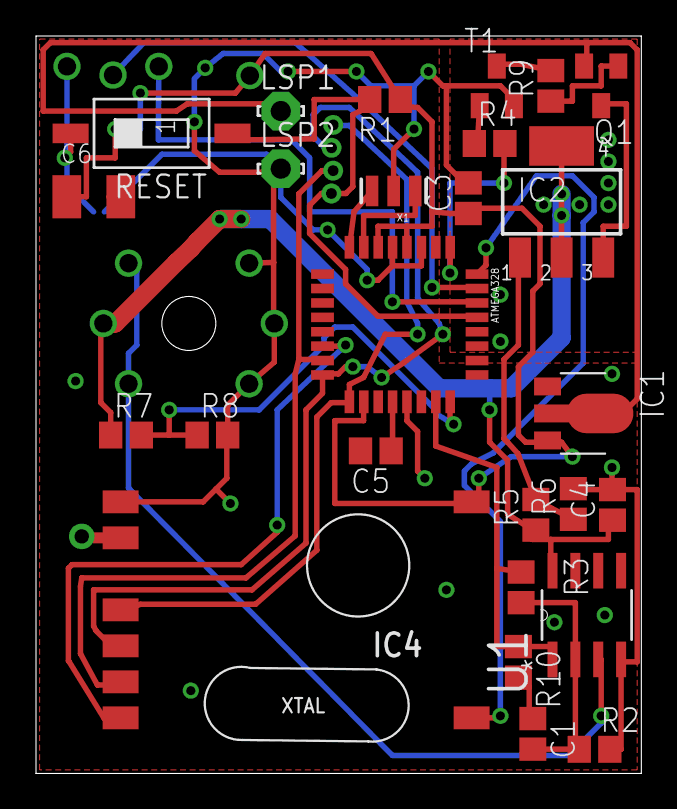
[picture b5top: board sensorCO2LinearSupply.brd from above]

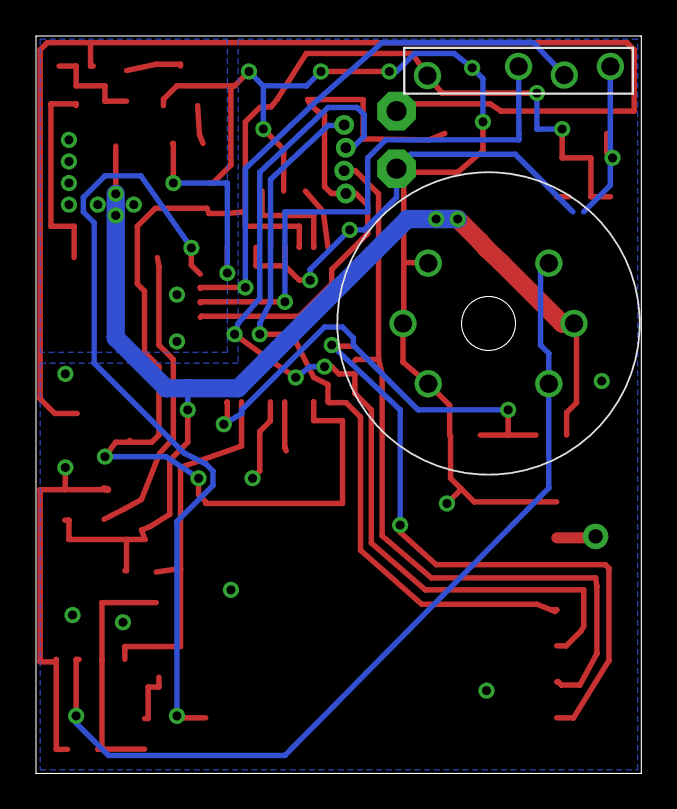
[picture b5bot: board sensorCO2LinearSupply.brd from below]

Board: 2 copper layers, 33.6 x 41.0 mm, 30 parts (2 on the bottom side), 27 nets.

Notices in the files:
parts and their libraries:
eagle-library-edeca.net-v5: This is v1 and is licensed under the Creative Commons (Attribution-Non-Commercial-Share Alike 2.0 UK)
SparkFun-Sensors: Licensing: Creative Commons ShareAlike 4.0 International - https://creativecommons.org/licenses/by-sa/4.0
